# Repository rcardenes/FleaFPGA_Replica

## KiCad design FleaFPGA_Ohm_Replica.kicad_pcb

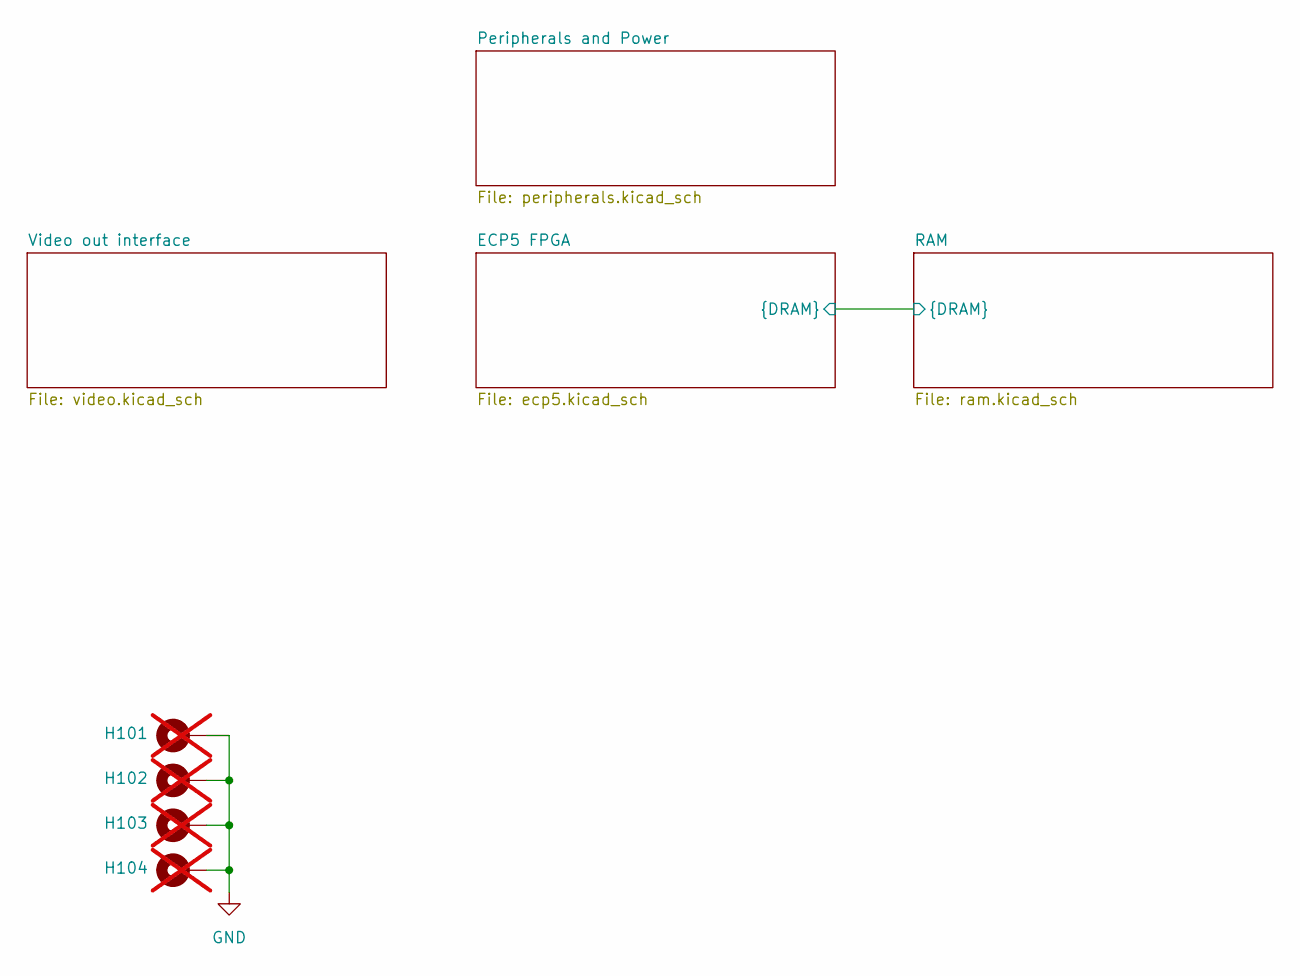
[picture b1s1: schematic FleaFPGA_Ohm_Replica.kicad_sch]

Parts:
H101, H102, H103, H104: MountingHole_Pad; MountingHole_2.7mm_M2.5_Pad; not fitted

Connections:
GND: H101.1, H102.1, H103.1, H104.1; also elsewhere on the board

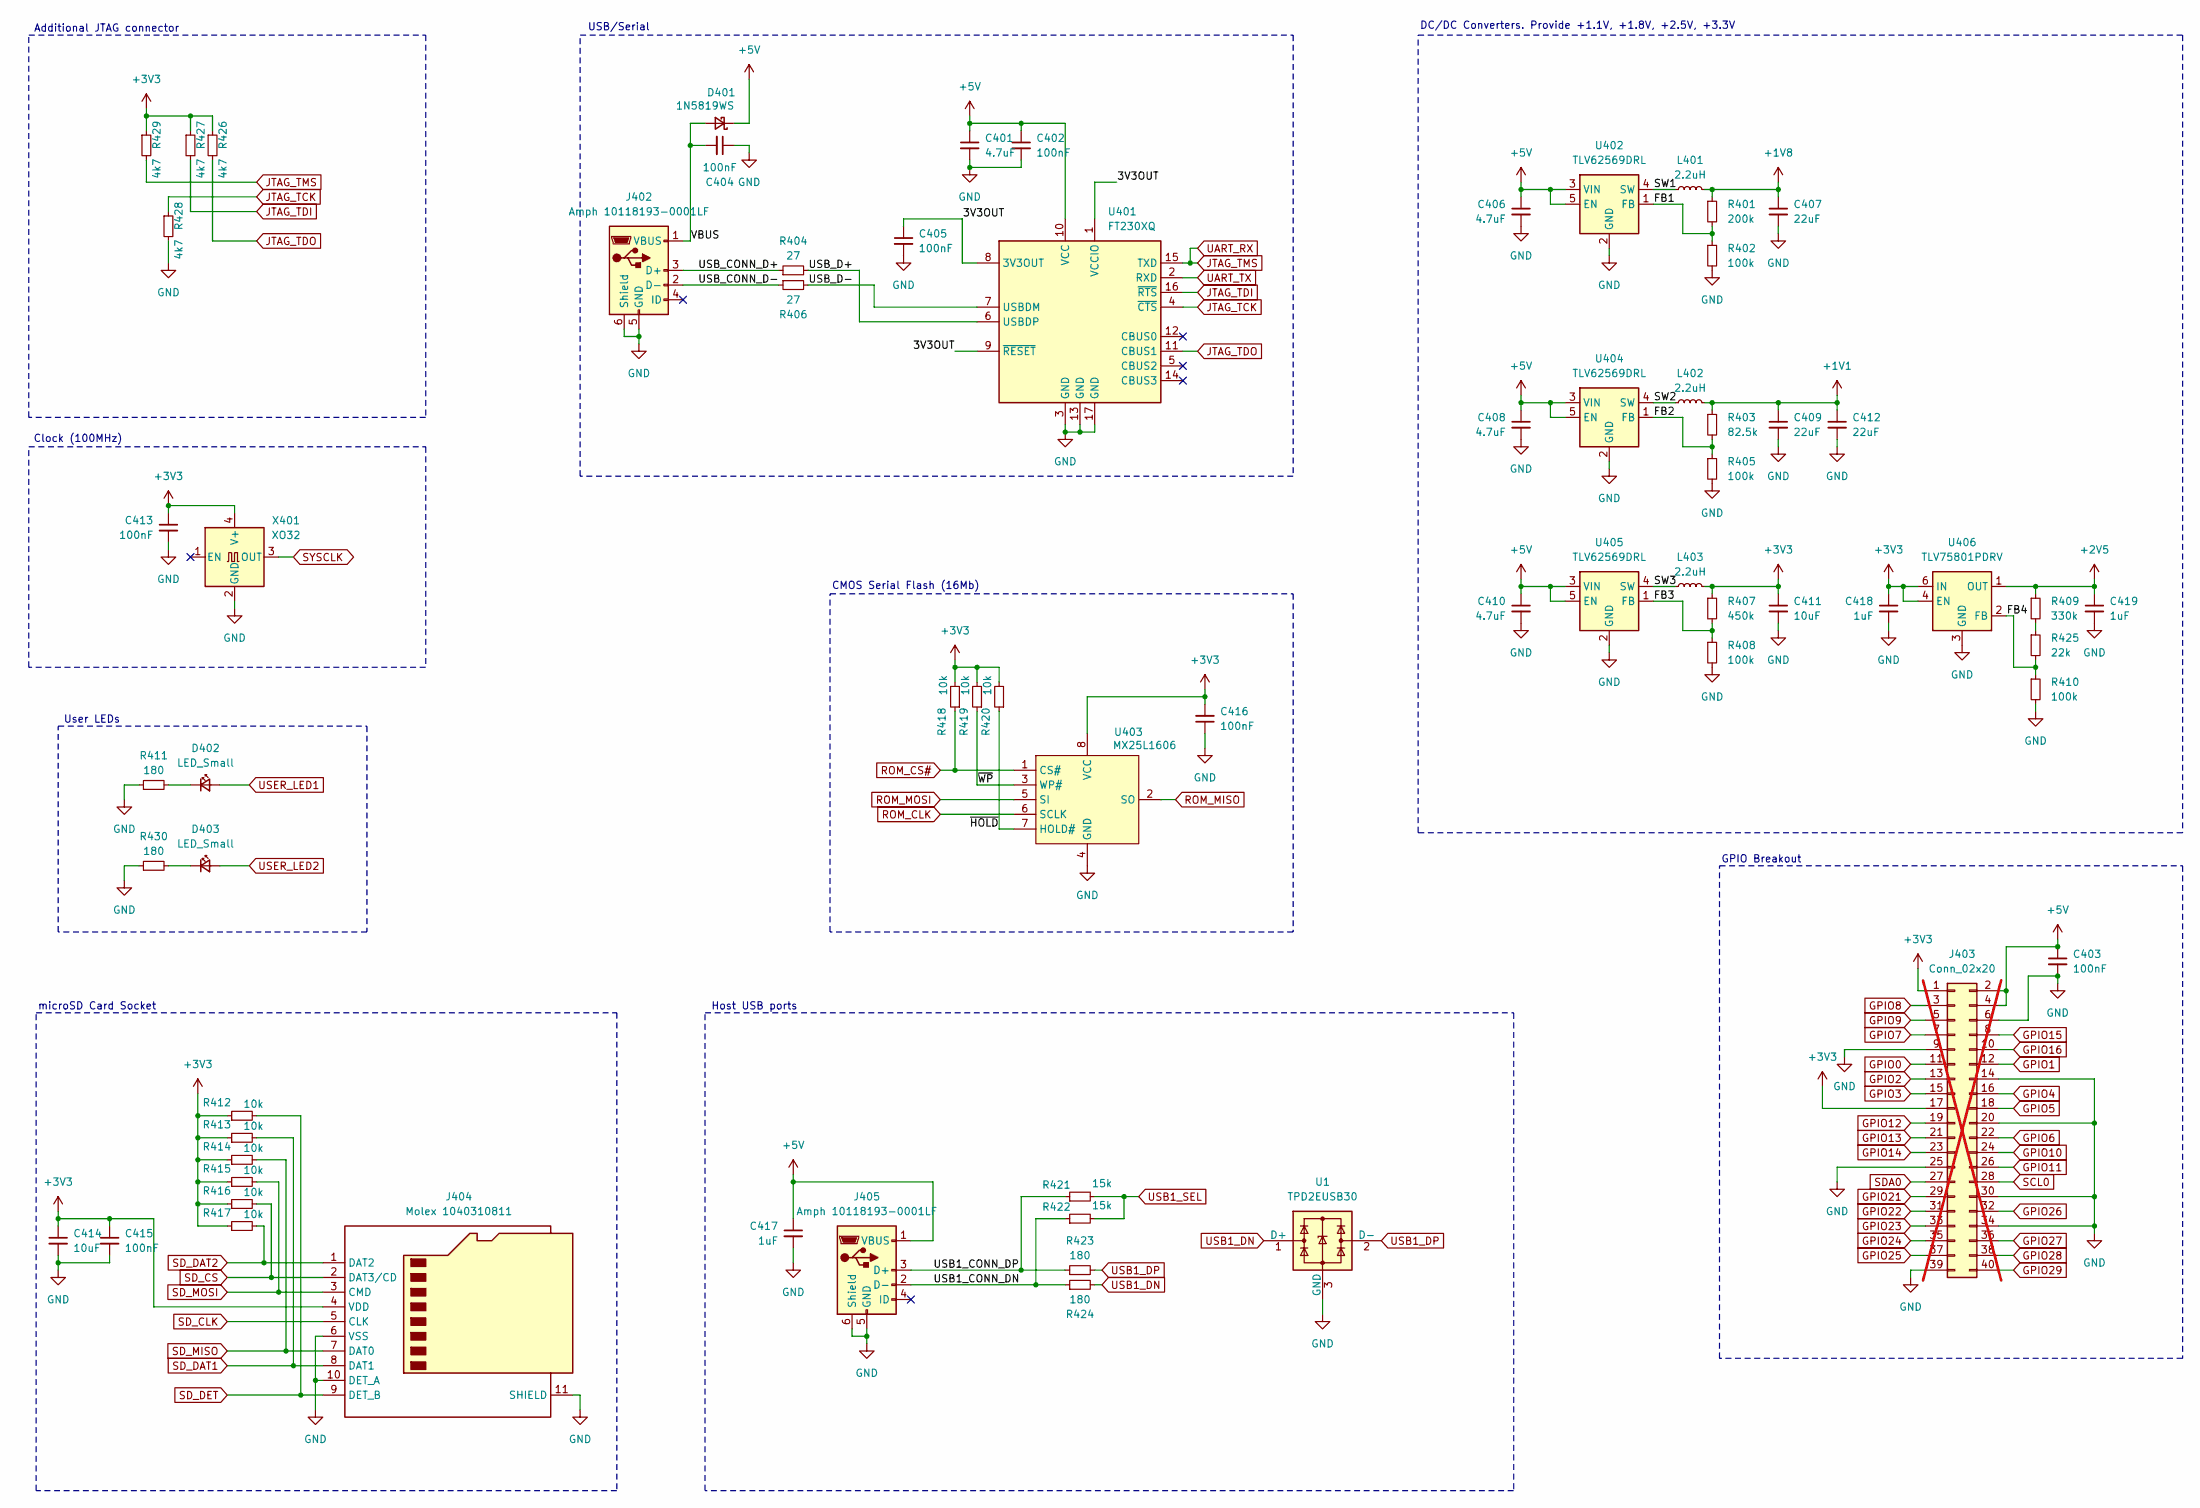
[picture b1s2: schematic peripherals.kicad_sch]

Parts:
C401, C406, C408, C410: 4.7uF; C_0603_1608Metric; MPN C19666
C402, C405, C413, C415, C416: 100nF; C_0201_0603Metric; MPN C190183
C403: 100nF; C_0603_1608Metric; MPN C14663
C404: 100nF; C_0402_1005Metric; MPN C1525
C407, C409, C412: 22uF; C_0603_1608Metric; MPN C59461
C411, C414: 10uF; C_0603_1608Metric; MPN C19702
C417: 1uF; C_0603_1608Metric; MPN C15849
C418, C419: 1uF; C_0402_1005Metric; MPN C52923
D401: 1N5819WS; D_SOD-323; MPN C191023
D402: LED_Small; LED_0603_1608Metric; MPN C2286
D403: LED_Small; LED_0603_1608Metric; MPN C72038
J402, J405: Amph 10118193-0001LF; USB_Micro-B_Amphenol_10118193-0001LF_Horizontal; MPN C132562
J403: Conn_02x20; PinHeader_2x20_P2.54mm_Vertical; not fitted
J404: Molex 1040310811; microSD_HC_Molex_104031-0811; MPN C585350
L401, L402, L403: 2.2uH; L_0805_2012Metric; MPN C383369
R401: 200k; R_0402_1005Metric; MPN C25764
R402, R405, R408, R410: 100k; R_0402_1005Metric; MPN C25741
R403: 82.5k; R_0402_1005Metric; MPN C11717
R404, R406: 27; R_0402_1005Metric; MPN C25100
R407: 450k; R_0402_1005Metric; MPN C5159688
R409: 330k; R_0603_1608Metric; MPN C23137
R411, R423, R424, R430: 180; R_0402_1005Metric; MPN C138045
R412, R413, R414, R415, R416, R417, R418, R419, R420: 10k; R_0402_1005Metric; MPN C25744
R421, R422: 15k; R_0402_1005Metric; MPN C25756
R425: 22k; R_0402_1005Metric; MPN C25768
R426, R427, R428, R429: 4k7; R_0402_1005Metric
U1: TPD2EUSB30; Texas_DRT-3; MPN C97502
U401: FT230XQ; QFN-16-1EP_4x4mm_P0.65mm_EP2.1x2.1mm; MPN C128629
U402, U404, U405: TLV62569DRL; SOT-563; MPN C163217
U403: MX25L1606; SOP-8-1EP_3.9x4.9mm_P1.27m_EP4.1x3.5mm; MPN C3014050
U406: TLV75801PDRV; WSON-6-1EP_2x2mm_P0.65mm_EP1x1.6mm; MPN C2876308
X401: XO32; Oscillator_SMD_XO32-4Pin_3.2x2.5mm; MPN C4353707

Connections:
+1V1: C409.1, C412.1, L402.2, R403.1; also elsewhere on the board
+1V8: C407.1, L401.2, R401.1; also elsewhere on the board
+2V5: C419.1, R409.1, U406.1 (OUT); also elsewhere on the board
+3V3: C411.1, C413.1, C414.1, C415.1, C416.2, C418.1, J403.1, J403.17, J404.4 (VDD), L403.2, R407.1, R412.1, R413.1, R414.1, R415.1, R416.1, R417.1, R418.2, R419.2, R420.2, R426.1, R427.1, R429.1, U403.8 (VCC), U406.4 (EN), U406.6 (IN), X401.4 (V+); also elsewhere on the board
+5V: C401.1, C402.1, C403.1, C406.1, C408.1, C410.1, C417.1, D401.1 (K), J403.2, J403.4, J405.1 (VBUS), U401.10 (VCC), U402.3 (VIN), U402.5 (EN), U404.3 (VIN), U404.5 (EN), U405.3 (VIN), U405.5 (EN); also elsewhere on the board
/Peripherals and Power/3V3OUT: C405.1, U401.1 (VCCIO), U401.8 (3V3OUT), U401.9 (~RESET)
/Peripherals and Power/FB1: R401.2, R402.1, U402.1 (FB)
/Peripherals and Power/FB2: R403.2, R405.1, U404.1 (FB)
/Peripherals and Power/FB3: R407.2, R408.1, U405.1 (FB)
/Peripherals and Power/FB4: R410.1, R425.2, U406.2 (FB)
/Peripherals and Power/SW1: L401.1, U402.4 (SW)
/Peripherals and Power/SW2: L402.1, U404.4 (SW)
/Peripherals and Power/SW3: L403.1, U405.4 (SW)
/Peripherals and Power/USB1_CONN_DN: J405.2 (D-), R422.1, R424.1
/Peripherals and Power/USB1_CONN_DP: J405.3 (D+), R421.1, R423.1
/Peripherals and Power/USB_CONN_D+: J402.3 (D+), R404.1
/Peripherals and Power/USB_CONN_D-: J402.2 (D-), R406.1
/Peripherals and Power/USB_D+: R404.2, U401.6 (USBDP)
/Peripherals and Power/USB_D-: R406.2, U401.7 (USBDM)
/Peripherals and Power/VBUS: C404.2, D401.2 (A), J402.1 (VBUS)
/Peripherals and Power/~HOLD: R420.1, U403.7 (HOLD#)
/Peripherals and Power/~WP: R419.1, U403.3 (WP#)
GND: C401.2, C402.2, C403.2, C404.1, C405.2, C406.2, C407.2, C408.2, C409.2, C410.2, C411.2, C412.2, C413.2, C414.2, C415.2, C416.1, C417.2, C418.2, C419.2, J402.5 (GND), J402.6 (Shield), J403.6, J403.9, J403.14, J403.20, J403.25, J403.30, J403.34, J403.39, J404.6 (VSS), J404.10 (DET_A), J404.11 (SHIELD), J405.5 (GND), J405.6 (Shield), R402.2, R405.2, R408.2, R410.2, R411.1, R428.2, R430.1, U1.3 (GND), U401.3 (GND), U401.13 (GND), U401.17 (GND), U402.2 (GND), U403.4 (GND), U404.2 (GND), U405.2 (GND), U406.3 (GND), U406.7 (GND), X401.2 (GND); also elsewhere on the board
GPIO0: J403.11; also elsewhere on the board
GPIO1: J403.12; also elsewhere on the board
GPIO2: J403.13; also elsewhere on the board
GPIO3: J403.15; also elsewhere on the board
GPIO4: J403.16; also elsewhere on the board
GPIO5: J403.18; also elsewhere on the board
GPIO6: J403.22; also elsewhere on the board
GPIO7: J403.7; also elsewhere on the board
GPIO8: J403.3; also elsewhere on the board
GPIO9: J403.5; also elsewhere on the board
GPIO10: J403.24; also elsewhere on the board
GPIO11: J403.26; also elsewhere on the board
GPIO12: J403.19; also elsewhere on the board
GPIO13: J403.21; also elsewhere on the board
GPIO14: J403.23; also elsewhere on the board
GPIO15: J403.8; also elsewhere on the board
GPIO16: J403.10; also elsewhere on the board
GPIO21: J403.29; also elsewhere on the board
GPIO22: J403.31; also elsewhere on the board
GPIO23: J403.33; also elsewhere on the board
GPIO24: J403.35
GPIO25: J403.37; also elsewhere on the board
GPIO26: J403.32; also elsewhere on the board
GPIO27: J403.36
GPIO28: J403.38; also elsewhere on the board
GPIO29: J403.40; also elsewhere on the board
JTAG_TCK: R428.1, U401.4 (~CTS); also elsewhere on the board
JTAG_TDI: R427.2, U401.16 (~RTS); also elsewhere on the board
JTAG_TDO: R426.2, U401.11 (CBUS1); also elsewhere on the board
JTAG_TMS: R429.2, U401.15 (TXD); also elsewhere on the board
unnamed: D402.1 (K), R411.2
unnamed: D403.1 (K), R430.2
unnamed: R409.2, R425.1
ROM_CLK: U403.6 (SCLK); also elsewhere on the board
ROM_CS#: R418.1, U403.1 (CS#); also elsewhere on the board
ROM_MISO: U403.2 (SO); also elsewhere on the board
ROM_MOSI: U403.5 (SI); also elsewhere on the board
SCL0: J403.28; also elsewhere on the board
SDA0: J403.27; also elsewhere on the board
SD_CLK: J404.5 (CLK); also elsewhere on the board
SD_CS: J404.2 (DAT3/CD), R416.2; also elsewhere on the board
SD_DAT1: J404.8 (DAT1), R413.2; also elsewhere on the board
SD_DAT2: J404.1 (DAT2), R417.2; also elsewhere on the board
SD_DET: J404.9 (DET_B), R412.2; also elsewhere on the board
SD_MISO: J404.7 (DAT0), R414.2; also elsewhere on the board
SD_MOSI: J404.3 (CMD), R415.2; also elsewhere on the board
SYSCLK: X401.3 (OUT); also elsewhere on the board
UART_TX: U401.2 (RXD); also elsewhere on the board
USB1_DN: R424.2, U1.1 (D+); also elsewhere on the board
USB1_DP: R423.2, U1.2 (D-); also elsewhere on the board
USB1_SEL: R421.2, R422.2; also elsewhere on the board
USER_LED1: D402.2 (A); also elsewhere on the board
USER_LED2: D403.2 (A); also elsewhere on the board

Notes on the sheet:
User LEDs
microSD Card Socket
Clock (100MHz)
Additional JTAG connector
USB/Serial
Host USB ports
CMOS Serial Flash (16Mb)
DC/DC Converters. Provide +1.1V, +1.8V, +2.5V, +3.3V
GPIO Breakout

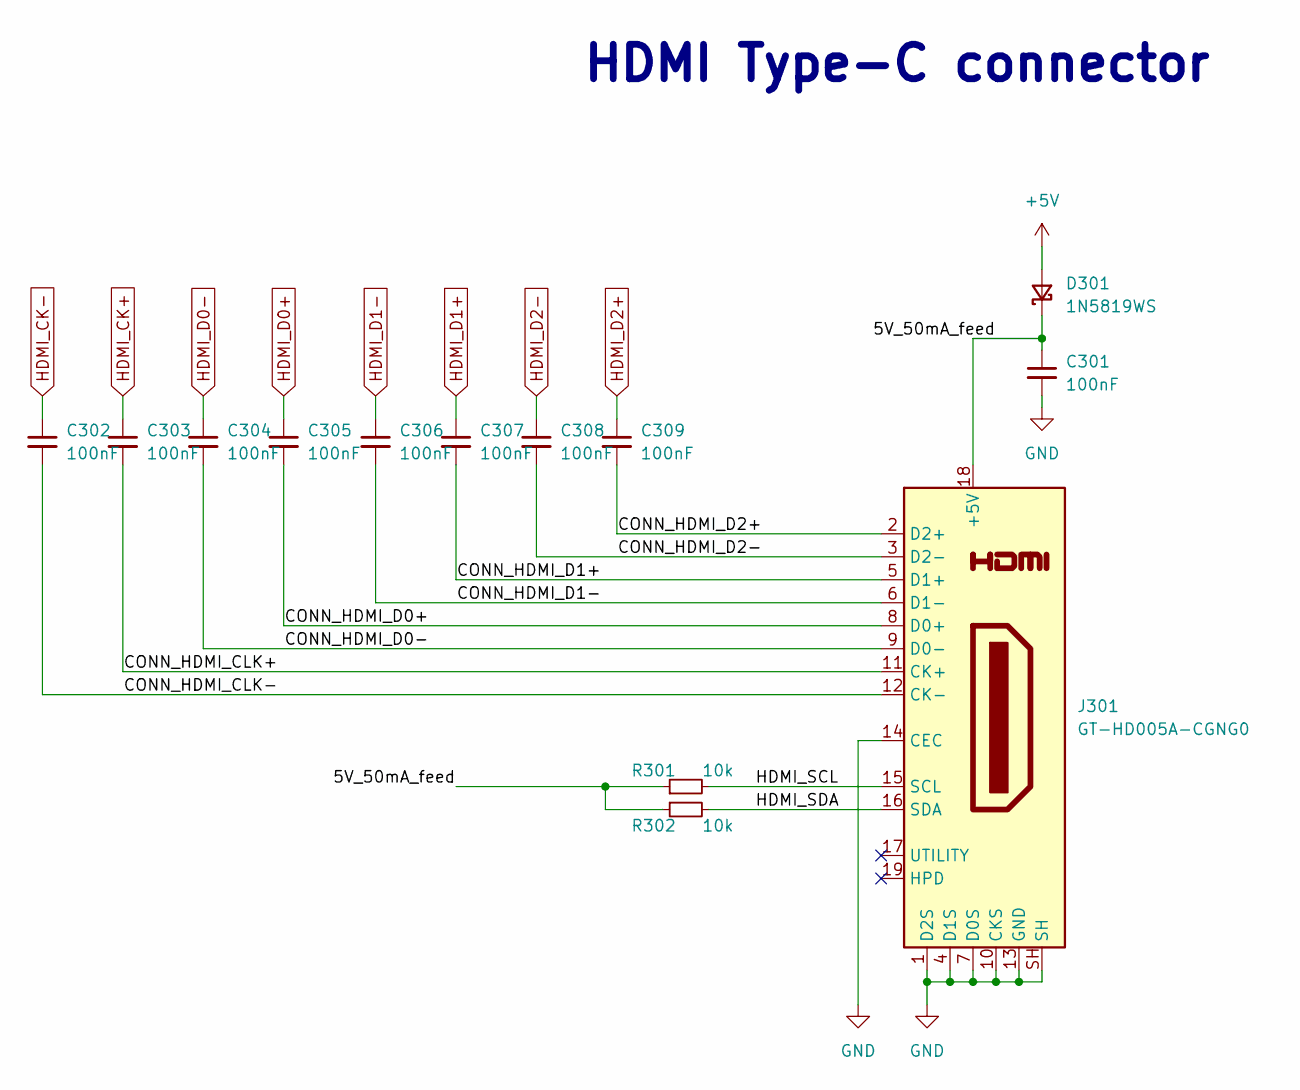
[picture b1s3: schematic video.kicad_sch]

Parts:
C301, C302, C303, C304, C305, C306, C307, C308, C309: 100nF; C_0201_0603Metric; MPN C190183
D301: 1N5819WS; D_SOD-323; MPN C191023
J301: GT-HD005A-CGNG0; GT-HD005A; MPN C27636754
R301, R302: 10k; R_0402_1005Metric; MPN C25744

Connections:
+5V: D301.2 (A); also elsewhere on the board
/Video out interface/5V_50mA_feed: C301.1, D301.1 (K), J301.18 (+5V), R301.1, R302.1
/Video out interface/CONN_HDMI_CLK+: C303.2, J301.11 (CK+)
/Video out interface/CONN_HDMI_CLK-: C302.2, J301.12 (CK-)
/Video out interface/CONN_HDMI_D0+: C305.2, J301.8 (D0+)
/Video out interface/CONN_HDMI_D0-: C304.2, J301.9 (D0-)
/Video out interface/CONN_HDMI_D1+: C307.2, J301.5 (D1+)
/Video out interface/CONN_HDMI_D1-: C306.2, J301.6 (D1-)
/Video out interface/CONN_HDMI_D2+: C309.2, J301.2 (D2+)
/Video out interface/CONN_HDMI_D2-: C308.2, J301.3 (D2-)
/Video out interface/HDMI_SCL: J301.15 (SCL), R301.2
/Video out interface/HDMI_SDA: J301.16 (SDA), R302.2
GND: C301.2, J301.1 (D2S), J301.4 (D1S), J301.7 (D0S), J301.10 (CKS), J301.13 (GND), J301.14 (CEC), J301.SH; also elsewhere on the board
HDMI_CK+: C303.1; also elsewhere on the board
HDMI_CK-: C302.1; also elsewhere on the board
HDMI_D0+: C305.1; also elsewhere on the board
HDMI_D0-: C304.1; also elsewhere on the board
HDMI_D1+: C307.1; also elsewhere on the board
HDMI_D1-: C306.1; also elsewhere on the board
HDMI_D2+: C309.1; also elsewhere on the board
HDMI_D2-: C308.1; also elsewhere on the board

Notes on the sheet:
HDMI Type-C connector

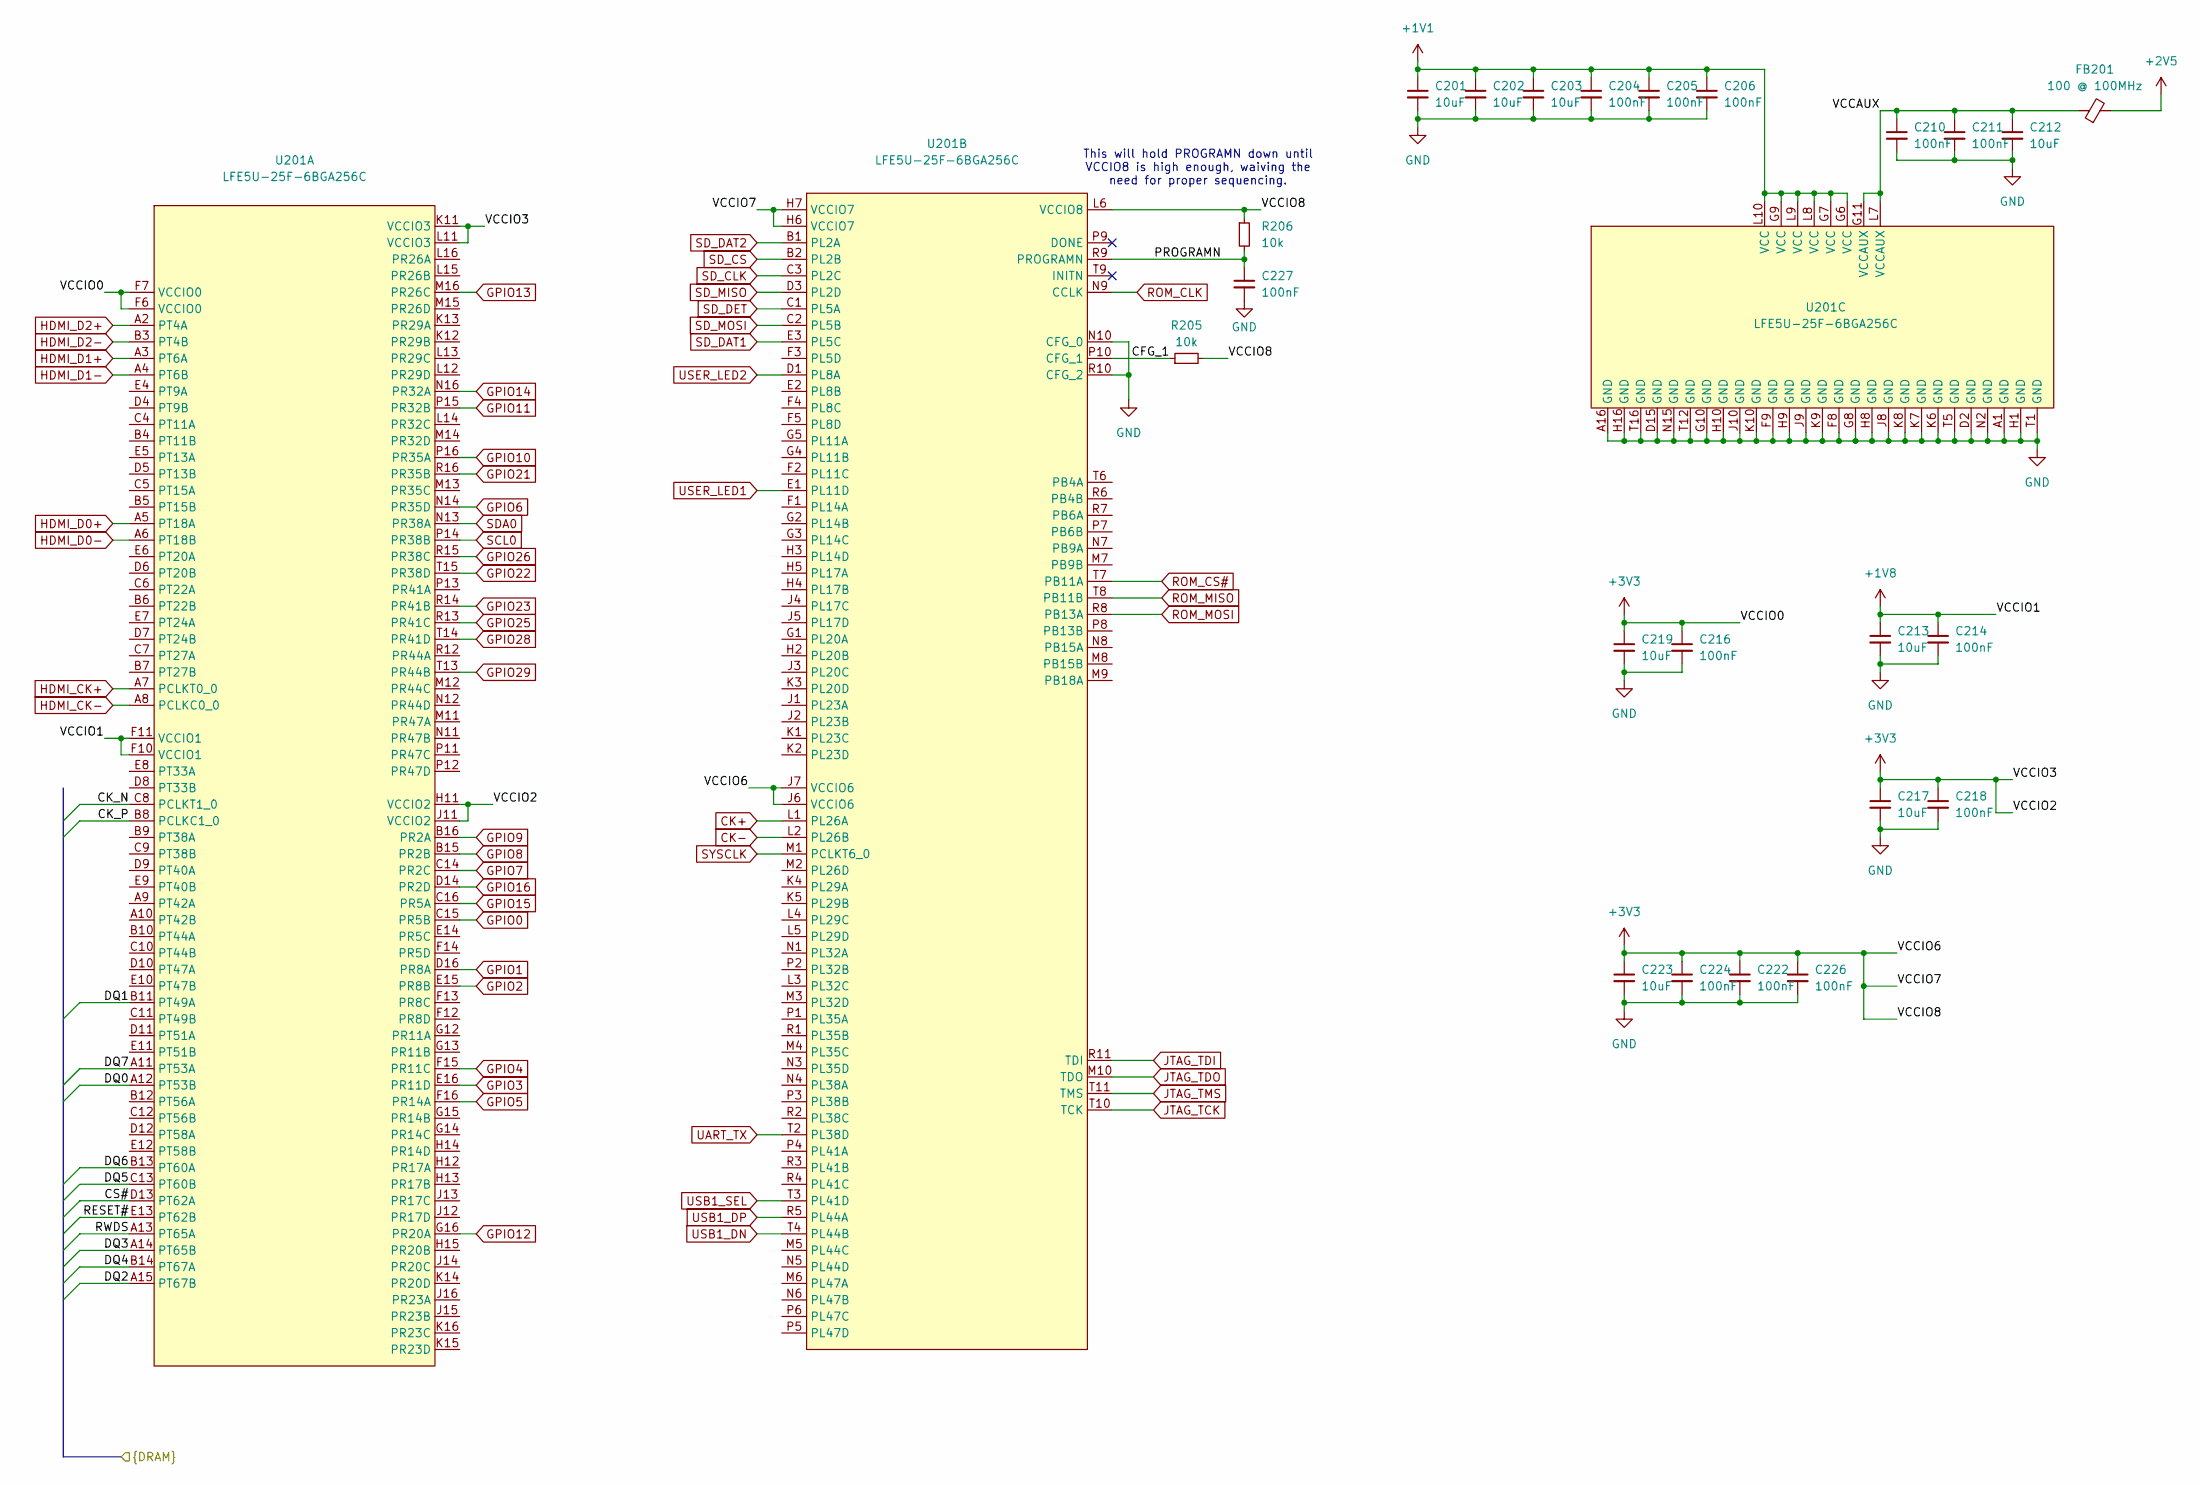
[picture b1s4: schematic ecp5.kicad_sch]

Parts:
C201, C202, C203, C212, C213, C217, C219, C223: 10uF; C_0402_1005Metric; MPN C15525
C204, C205, C206, C210, C211, C214, C216, C218, C222, C224, C226, C227: 100nF; C_0201_0603Metric; MPN C190183
FB201: 100 @ 100MHz; L_0805_2012Metric; MPN C1015
R205, R206: 10k; R_0201_0603Metric; MPN C473048
U201: LFE5U-25F-6BGA256C; Lattice_caBGA-256_14.0x14.0mm_Layout16x16_P0.8mm; MPN C1521614

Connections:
+1V1: C201.1, C202.1, C203.1, C204.1, C205.1, C206.1, U201.G6 (VCC), U201.G7 (VCC), U201.G9 (VCC), U201.L8 (VCC), U201.L9 (VCC), U201.L10 (VCC); also elsewhere on the board
+1V8: C213.1, C214.1, U201.F10 (VCCIO1), U201.F11 (VCCIO1); also elsewhere on the board
+2V5: FB201.2; also elsewhere on the board
+3V3: C216.1, C217.1, C218.1, C219.1, C222.1, C223.1, C224.1, C226.1, R205.2, R206.1, U201.F6 (VCCIO0), U201.F7 (VCCIO0), U201.H6 (VCCIO7), U201.H7 (VCCIO7), U201.H11 (VCCIO2), U201.J6 (VCCIO6), U201.J7 (VCCIO6), U201.J11 (VCCIO2), U201.K11 (VCCIO3), U201.L6 (VCCIO8), U201.L11 (VCCIO3); also elsewhere on the board
/ECP5 FPGA/CFG_1: R205.1, U201.P10 (CFG_1)
/ECP5 FPGA/CK_N: U201.C8 (PCLKT1_0); also elsewhere on the board
/ECP5 FPGA/CK_P: U201.B8 (PCLKC1_0); also elsewhere on the board
/ECP5 FPGA/CS#: U201.D13 (PT62A); also elsewhere on the board
/ECP5 FPGA/DQ0: U201.A12 (PT53B); also elsewhere on the board
/ECP5 FPGA/DQ1: U201.B11 (PT49A); also elsewhere on the board
/ECP5 FPGA/DQ2: U201.A15 (PT67B); also elsewhere on the board
/ECP5 FPGA/DQ3: U201.A14 (PT65B); also elsewhere on the board
/ECP5 FPGA/DQ4: U201.B14 (PT67A); also elsewhere on the board
/ECP5 FPGA/DQ5: U201.C13 (PT60B); also elsewhere on the board
/ECP5 FPGA/DQ6: U201.B13 (PT60A); also elsewhere on the board
/ECP5 FPGA/DQ7: U201.A11 (PT53A); also elsewhere on the board
/ECP5 FPGA/PROGRAMN: C227.1, R206.2, U201.R9 (PROGRAMN)
/ECP5 FPGA/RESET#: U201.E13 (PT62B); also elsewhere on the board
/ECP5 FPGA/RWDS: U201.A13 (PT65A); also elsewhere on the board
/ECP5 FPGA/VCCAUX: C210.1, C211.1, C212.1, FB201.1, U201.G11 (VCCAUX), U201.L7 (VCCAUX)
CK+: U201.L1 (PL26A)
CK-: U201.L2 (PL26B)
GND: C201.2, C202.2, C203.2, C204.2, C205.2, C206.2, C210.2, C211.2, C212.2, C213.2, C214.2, C216.2, C217.2, C218.2, C219.2, C222.2, C223.2, C224.2, C226.2, C227.2, U201.A1 (GND), U201.A16 (GND), U201.D2 (GND), U201.D15 (GND), U201.F8 (GND), U201.F9 (GND), U201.G8 (GND), U201.G10 (GND), U201.H1 (GND), U201.H8 (GND), U201.H9 (GND), U201.H10 (GND), U201.H16 (GND), U201.J8 (GND), U201.J9 (GND), U201.J10 (GND), U201.K6 (GND), U201.K7 (GND), U201.K8 (GND), U201.K9 (GND), U201.K10 (GND), U201.N2 (GND), U201.N10 (CFG_0), U201.N15 (GND), U201.R10 (CFG_2), U201.T1 (GND), U201.T5 (GND), U201.T12 (GND), U201.T16 (GND); also elsewhere on the board
GPIO0: U201.C15 (PR5B); also elsewhere on the board
GPIO1: U201.D16 (PR8A); also elsewhere on the board
GPIO2: U201.E15 (PR8B); also elsewhere on the board
GPIO3: U201.E16 (PR11D); also elsewhere on the board
GPIO4: U201.F15 (PR11C); also elsewhere on the board
GPIO5: U201.F16 (PR14A); also elsewhere on the board
GPIO6: U201.N14 (PR35D); also elsewhere on the board
GPIO7: U201.C14 (PR2C); also elsewhere on the board
GPIO8: U201.B15 (PR2B); also elsewhere on the board
GPIO9: U201.B16 (PR2A); also elsewhere on the board
GPIO10: U201.P16 (PR35A); also elsewhere on the board
GPIO11: U201.P15 (PR32B); also elsewhere on the board
GPIO12: U201.G16 (PR20A); also elsewhere on the board
GPIO13: U201.M16 (PR26C); also elsewhere on the board
GPIO14: U201.N16 (PR32A); also elsewhere on the board
GPIO15: U201.C16 (PR5A); also elsewhere on the board
GPIO16: U201.D14 (PR2D); also elsewhere on the board
GPIO21: U201.R16 (PR35B); also elsewhere on the board
GPIO22: U201.T15 (PR38D); also elsewhere on the board
GPIO23: U201.R14 (PR41B); also elsewhere on the board
GPIO25: U201.R13 (PR41C); also elsewhere on the board
GPIO26: U201.R15 (PR38C); also elsewhere on the board
GPIO28: U201.T14 (PR41D); also elsewhere on the board
GPIO29: U201.T13 (PR44B); also elsewhere on the board
HDMI_CK+: U201.A7 (PCLKT0_0); also elsewhere on the board
HDMI_CK-: U201.A8 (PCLKC0_0); also elsewhere on the board
HDMI_D0+: U201.A5 (PT18A); also elsewhere on the board
HDMI_D0-: U201.A6 (PT18B); also elsewhere on the board
HDMI_D1+: U201.A3 (PT6A); also elsewhere on the board
HDMI_D1-: U201.A4 (PT6B); also elsewhere on the board
HDMI_D2+: U201.A2 (PT4A); also elsewhere on the board
HDMI_D2-: U201.B3 (PT4B); also elsewhere on the board
JTAG_TCK: U201.T10 (TCK); also elsewhere on the board
JTAG_TDI: U201.R11 (TDI); also elsewhere on the board
JTAG_TDO: U201.M10 (TDO); also elsewhere on the board
JTAG_TMS: U201.T11 (TMS); also elsewhere on the board
ROM_CLK: U201.N9 (CCLK); also elsewhere on the board
ROM_CS#: U201.T7 (PB11A); also elsewhere on the board
ROM_MISO: U201.T8 (PB11B); also elsewhere on the board
ROM_MOSI: U201.R8 (PB13A); also elsewhere on the board
SCL0: U201.P14 (PR38B); also elsewhere on the board
SDA0: U201.N13 (PR38A); also elsewhere on the board
SD_CLK: U201.C3 (PL2C); also elsewhere on the board
SD_CS: U201.B2 (PL2B); also elsewhere on the board
SD_DAT1: U201.E3 (PL5C); also elsewhere on the board
SD_DAT2: U201.B1 (PL2A); also elsewhere on the board
SD_DET: U201.C1 (PL5A); also elsewhere on the board
SD_MISO: U201.D3 (PL2D); also elsewhere on the board
SD_MOSI: U201.C2 (PL5B); also elsewhere on the board
SYSCLK: U201.M1 (PCLKT6_0); also elsewhere on the board
UART_TX: U201.T2 (PL38D); also elsewhere on the board
USB1_DN: U201.T4 (PL44B); also elsewhere on the board
USB1_DP: U201.R5 (PL44A); also elsewhere on the board
USB1_SEL: U201.T3 (PL41D); also elsewhere on the board
USER_LED1: U201.E1 (PL11D); also elsewhere on the board
USER_LED2: U201.D1 (PL8A); also elsewhere on the board

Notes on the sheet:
This will hold PROGRAMN down until VCCIO8 is high enough, waiving the need for proper sequencing.

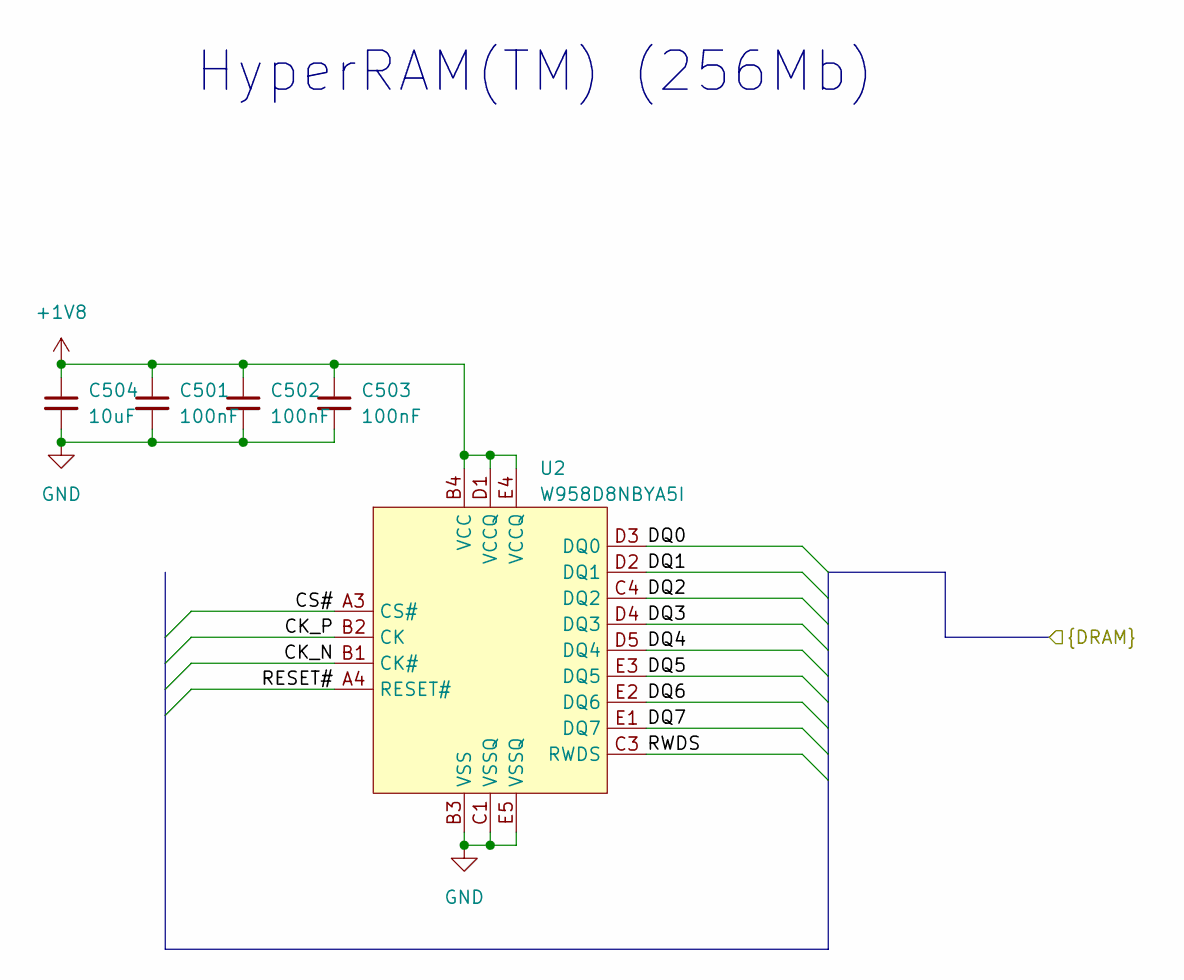
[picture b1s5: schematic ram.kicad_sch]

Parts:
C501, C502, C503: 100nF; C_0402_1005Metric; MPN C1525
C504: 10uF; C_0402_1005Metric; MPN C15525
U2: W958D8NBYA5I; FBGA-25_8x6mm_Layout5x6_P1mm; MPN C7420405

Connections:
+1V8: C501.1, C502.1, C503.1, C504.1, U2.B4 (VCC), U2.D1 (VCCQ), U2.E4 (VCCQ); also elsewhere on the board
/ECP5 FPGA/CK_N: U2.B1 (CK#); also elsewhere on the board
/ECP5 FPGA/CK_P: U2.B2 (CK); also elsewhere on the board
/ECP5 FPGA/CS#: U2.A3 (CS#); also elsewhere on the board
/ECP5 FPGA/DQ0: U2.D3 (DQ0); also elsewhere on the board
/ECP5 FPGA/DQ1: U2.D2 (DQ1); also elsewhere on the board
/ECP5 FPGA/DQ2: U2.C4 (DQ2); also elsewhere on the board
/ECP5 FPGA/DQ3: U2.D4 (DQ3); also elsewhere on the board
/ECP5 FPGA/DQ4: U2.D5 (DQ4); also elsewhere on the board
/ECP5 FPGA/DQ5: U2.E3 (DQ5); also elsewhere on the board
/ECP5 FPGA/DQ6: U2.E2 (DQ6); also elsewhere on the board
/ECP5 FPGA/DQ7: U2.E1 (DQ7); also elsewhere on the board
/ECP5 FPGA/RESET#: U2.A4 (RESET#); also elsewhere on the board
/ECP5 FPGA/RWDS: U2.C3 (RWDS); also elsewhere on the board
GND: C501.2, C502.2, C503.2, C504.2, U2.B3 (VSS), U2.C1 (VSSQ), U2.E5 (VSSQ); also elsewhere on the board

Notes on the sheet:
HyperRAM(TM) (256Mb)

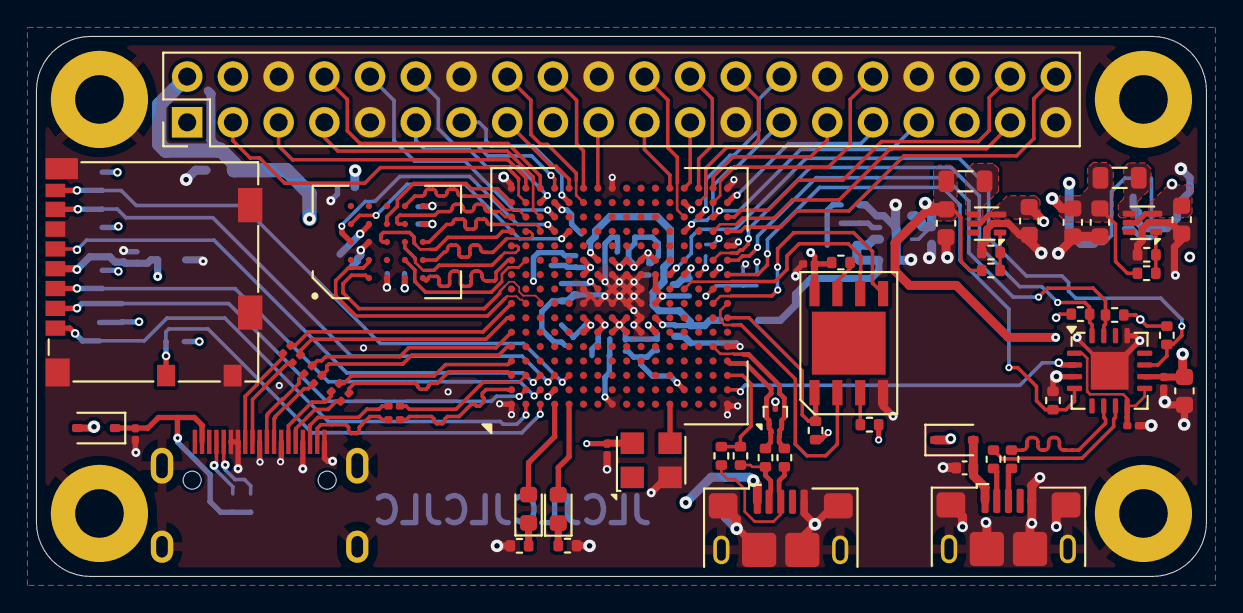
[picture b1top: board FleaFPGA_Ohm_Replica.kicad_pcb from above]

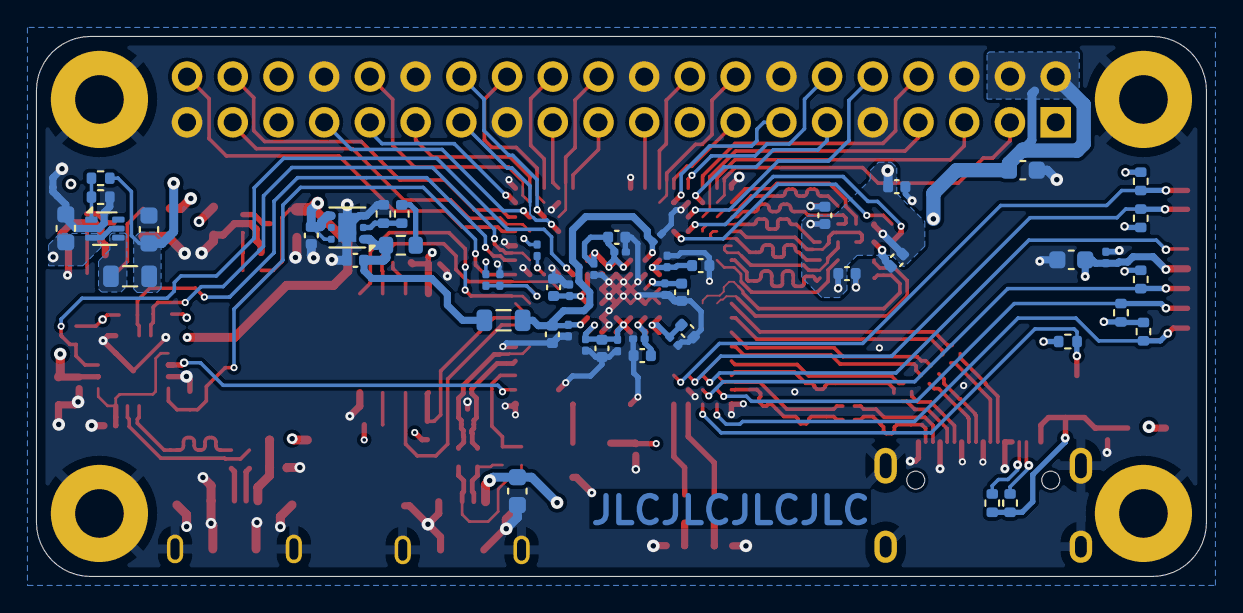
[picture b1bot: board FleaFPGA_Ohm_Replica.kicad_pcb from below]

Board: 4 copper layers, 65.0 x 30.0 mm, 113 parts (51 on the bottom side), 109 nets.

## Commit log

2024-09-13 First round at adapting the schematic. Missing the FPGA pads
2024-09-14 Cosmetics
2024-09-20 Towards routing RAM
    - Moved the RAM to its own sheet
    - Use the ECP5 prefix to capture impedance controlled traces
2024-10-08 First whole routing
2024-10-09 Update some component values and complete MPN for BOM
2024-10-11 Last minute changes before sending to JLCPCB
2024-11-16 Minor fixes
